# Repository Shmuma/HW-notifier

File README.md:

Simple FT232-based board to notify about events - it has three LEDs which can be controlled
independently.

Currently, only hardware part is ready, but I have plans to implement simple CLI
and Pidgin plugin to allow notify about incoming messages.

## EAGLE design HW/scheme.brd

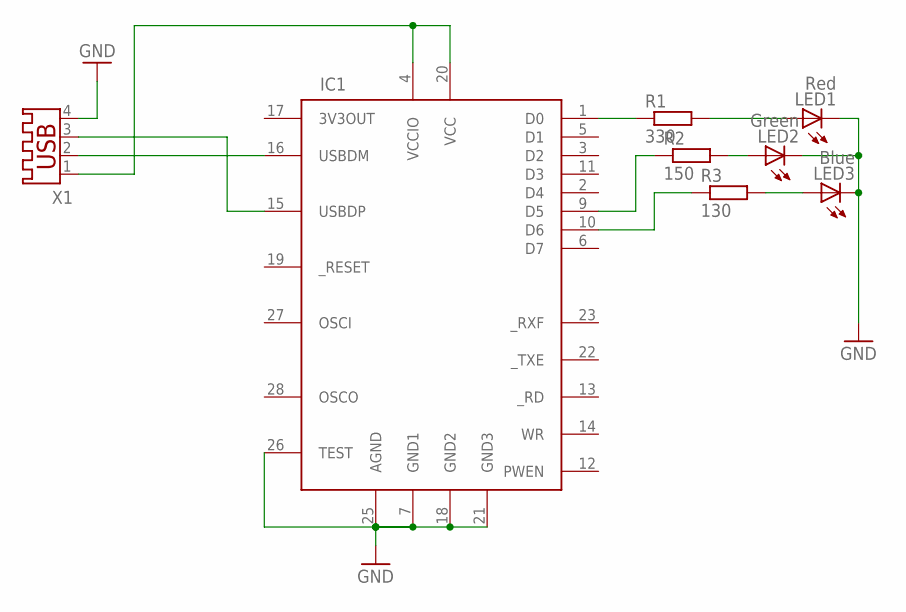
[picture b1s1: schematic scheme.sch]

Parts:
IC1: FT245RL; SSOP28DB
LED1: Red; NFSG036BT
LED2: Green; NFSG036BT
LED3: Blue; NFSG036BT
R1: 330; M1406
R2: 150; M1406
R3: 130; M1406
X1: USB-A003BOTTOM; USB-A003-BOTTOM

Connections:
GND: IC1.7 (GND1), IC1.18 (GND2), IC1.21 (GND3), IC1.25 (AGND), IC1.26 (TEST), LED1.C, LED2.C, LED3.C, X1.4 (GND-4)
unnamed: IC1.4 (VCCIO), IC1.20 (VCC), X1.1 (V+1)
unnamed: IC1.16 (USBDM), X1.2 (D-2)
unnamed: IC1.15 (USBDP), X1.3 (D+3)
unnamed: IC1.1 (D0), R1.1
unnamed: IC1.10 (D6), R3.1
unnamed: IC1.9 (D5), R2.1
unnamed: LED2.A, R2.2
unnamed: LED1.A, R1.2
unnamed: LED3.A, R3.2

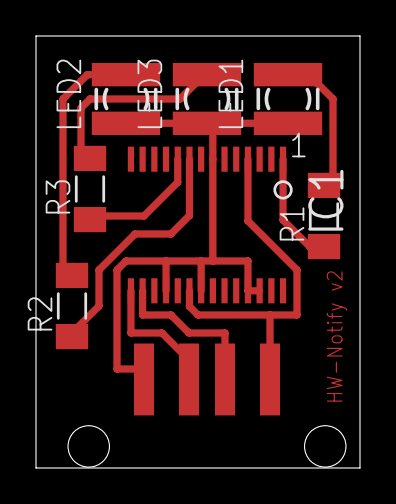
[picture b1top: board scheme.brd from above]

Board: 2 copper layers, 18.0 x 24.0 mm, 8 parts (1 on the bottom side), 10 nets.

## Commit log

2012-11-01 HW data
2012-11-01 CLI started
2012-11-01 CLI finished
2012-11-02 udev rule for user access
2012-11-02 Plugin started
2012-11-02 Notification implemented
2012-11-03 Plugin finished
2012-11-05 EEPROM update utility
2012-11-08 Hardware reinitialization
2012-11-10 Board v2
2012-11-11 Misc changes
2012-11-12 Fix error with buffered read data
